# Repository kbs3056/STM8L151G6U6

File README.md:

# STM8L151G6U6
STM8L151GxUx development board.

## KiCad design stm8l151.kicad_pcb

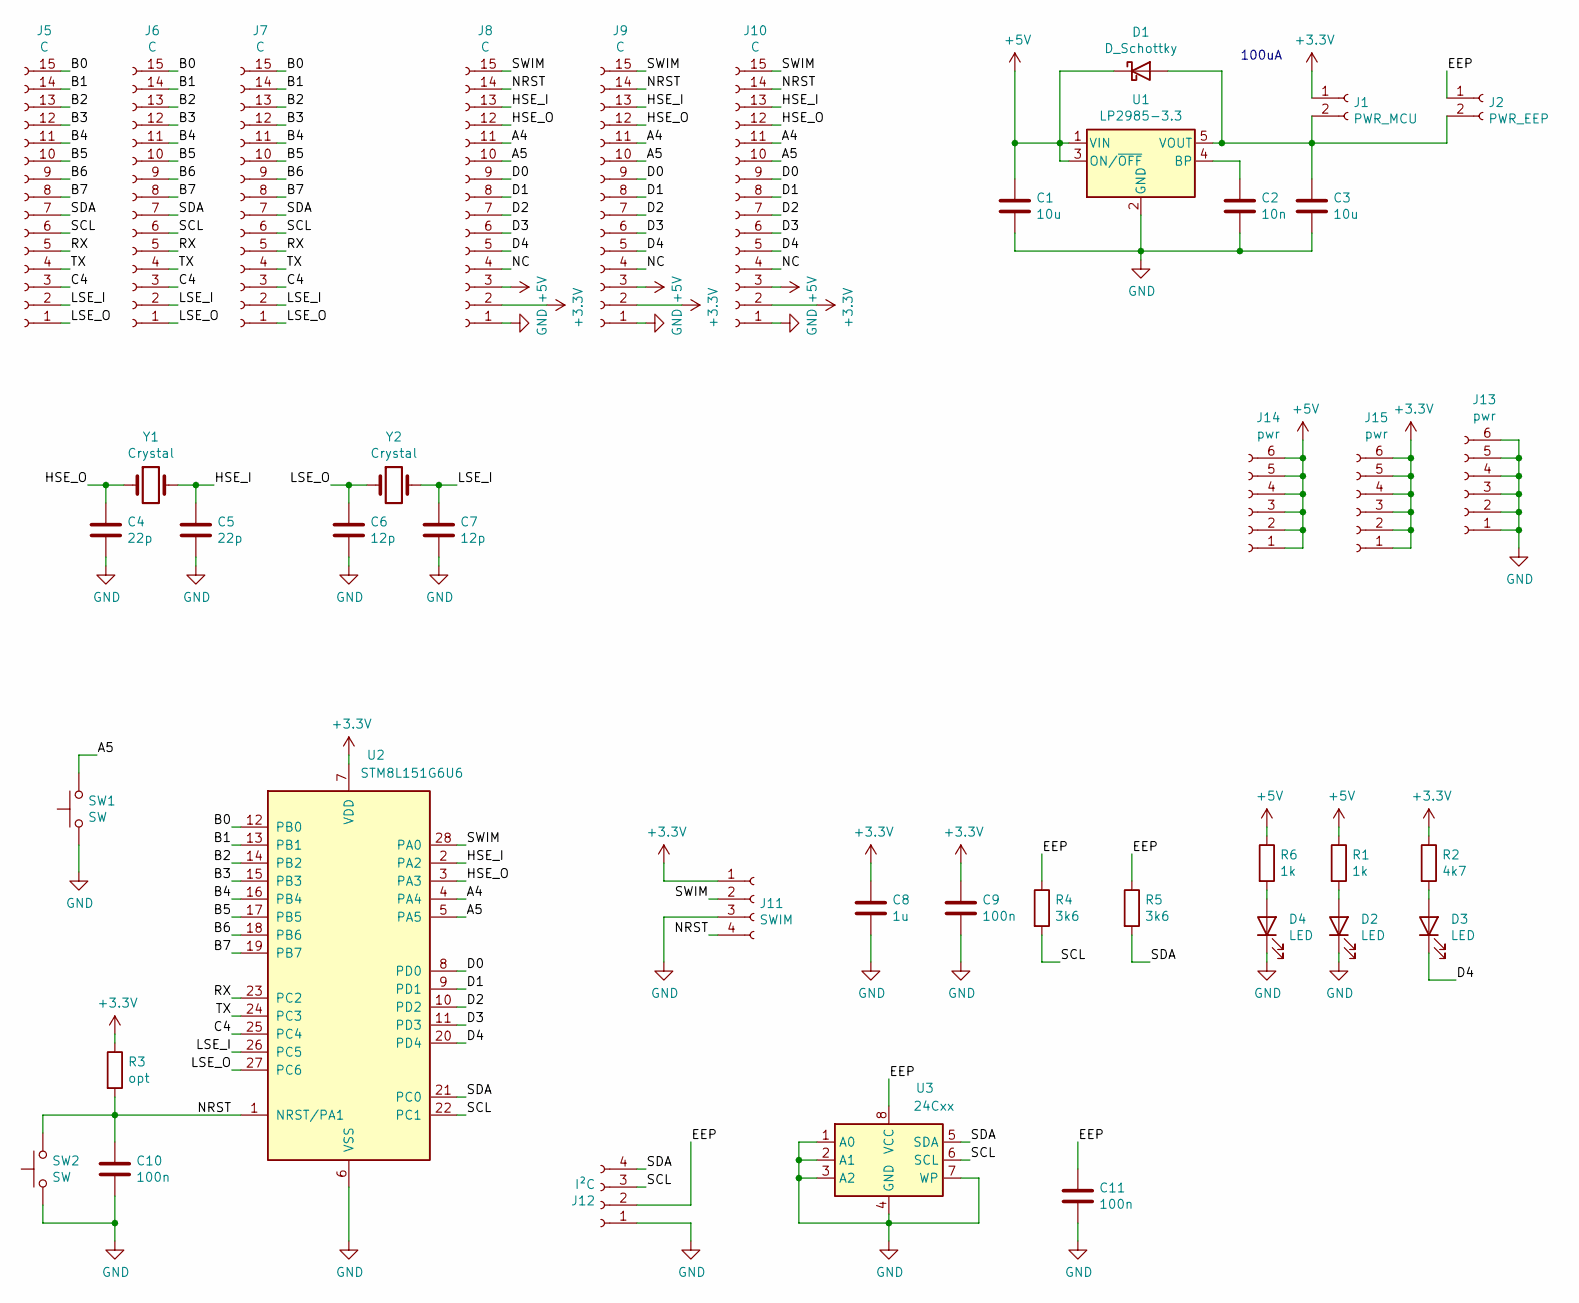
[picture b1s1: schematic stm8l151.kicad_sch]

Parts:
C1, C3: 10u; C_1206_3216Metric
C2: 10n; C_0805_2012Metric
C4, C5: 22p; C_0805_2012Metric
C6, C7: 12p; C_0805_2012Metric
C8: 1u; C_1206_3216Metric
C9, C10, C11: 100n; C_0805_2012Metric
D1: D_Schottky; D_MiniMELF
D2, D3, D4: LED; LED_0805_2012Metric
J1: PWR_MCU; PinSocket_1x02_P2.54mm_Vertical
J2: PWR_EEP; PinSocket_1x02_P2.54mm_Vertical
J5, J6, J7, J8, J9, J10: C; PinSocket_1x15_P2.54mm_Vertical
J11: SWIM; PinSocket_1x04_P2.54mm_Vertical
J12: I²C; PinSocket_1x04_P2.54mm_Vertical
J13, J14, J15: pwr; PinSocket_1x06_P2.54mm_Vertical
R1, R6: 1k; R_1206_3216Metric
R2: 4k7; R_1206_3216Metric
R3: opt; R_1206_3216Metric
R4, R5: 3k6; R_1206_3216Metric
SW1, SW2: SW; SW_SPST_CK_RS282G05A3
U1: LP2985-3.3; SOT-23-5
U2: STM8L151G6U6; QFN-28_4x4mm_P0.5mm
U3: 24Cxx; SOIC-8_5.23x5.23mm_P1.27mm
Y1: Crystal; Crystal_HC49-U_Horizontal
Y2: Crystal; Crystal_C26-LF_D2.1mm_L6.5mm_Horizontal

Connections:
+3V3: C8.1, C9.1, J1.1, J8.2, J9.2, J10.2, J11.1, J15.1, J15.2, J15.3, J15.4, J15.5, J15.6, R2.1, R3.1, U2.7 (VDD)
+5V: C1.1, D1.1 (K), J8.3, J9.3, J10.3, J14.1, J14.2, J14.3, J14.4, J14.5, J14.6, R1.1, R6.1, U1.1 (VIN), U1.3 (ON/~OFF)
/A4: J8.11, J9.11, J10.11, U2.4 (PA4)
/A5: J8.10, J9.10, J10.10, SW1.2, U2.5 (PA5)
/B0: J5.15, J6.15, J7.15, U2.12 (PB0)
/B1: J5.14, J6.14, J7.14, U2.13 (PB1)
/B2: J5.13, J6.13, J7.13, U2.14 (PB2)
/B3: J5.12, J6.12, J7.12, U2.15 (PB3)
/B4: J5.11, J6.11, J7.11, U2.16 (PB4)
/B5: J5.10, J6.10, J7.10, U2.17 (PB5)
/B6: J5.9, J6.9, J7.9, U2.18 (PB6)
/B7: J5.8, J6.8, J7.8, U2.19 (PB7)
/C4: J5.3, J6.3, J7.3, U2.25 (PC4)
/D0: J8.9, J9.9, J10.9, U2.8 (PD0)
/D1: J8.8, J9.8, J10.8, U2.9 (PD1)
/D2: J8.7, J9.7, J10.7, U2.10 (PD2)
/D3: J8.6, J9.6, J10.6, U2.11 (PD3)
/D4: D3.1 (K), J8.5, J9.5, J10.5, U2.20 (PD4)
/EEP: C11.1, J2.1, J12.2, R4.1, R5.1, U3.8 (VCC)
/HSE_I: C5.1, J8.13, J9.13, J10.13, U2.2 (PA2), Y1.2
/HSE_O: C4.1, J8.12, J9.12, J10.12, U2.3 (PA3), Y1.1
/LSE_I: C7.1, J5.2, J6.2, J7.2, U2.26 (PC5), Y2.2
/LSE_O: C6.1, J5.1, J6.1, J7.1, U2.27 (PC6), Y2.1
/NC: J8.4, J9.4, J10.4
/NRST: C10.1, J8.14, J9.14, J10.14, J11.4, R3.2, SW2.2, U2.1 (NRST/PA1)
/RX: J5.5, J6.5, J7.5, U2.23 (PC2)
/SCL: J5.6, J6.6, J7.6, J12.3, R4.2, U2.22 (PC1), U3.6 (SCL)
/SDA: J5.7, J6.7, J7.7, J12.4, R5.2, U2.21 (PC0), U3.5 (SDA)
/SWIM: J8.15, J9.15, J10.15, J11.2, U2.28 (PA0)
/TX: J5.4, J6.4, J7.4, U2.24 (PC3)
GND: C1.2, C2.2, C3.2, C4.2, C5.2, C6.2, C7.2, C8.2, C9.2, C10.2, C11.2, D2.1 (K), D4.1 (K), J8.1, J9.1, J10.1, J11.3, J12.1, J13.1, J13.2, J13.3, J13.4, J13.5, J13.6, SW1.1, SW2.1, U1.2 (GND), U2.6 (VSS), U3.1 (A0), U3.2 (A1), U3.3 (A2), U3.4 (GND), U3.7 (WP)
unnamed: C2.1, U1.4 (BP)
unnamed: C3.1, D1.2 (A), J1.2, J2.2, U1.5 (VOUT)
unnamed: D2.2 (A), R1.2
unnamed: D3.2 (A), R2.2
unnamed: D4.2 (A), R6.2

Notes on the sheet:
100uA

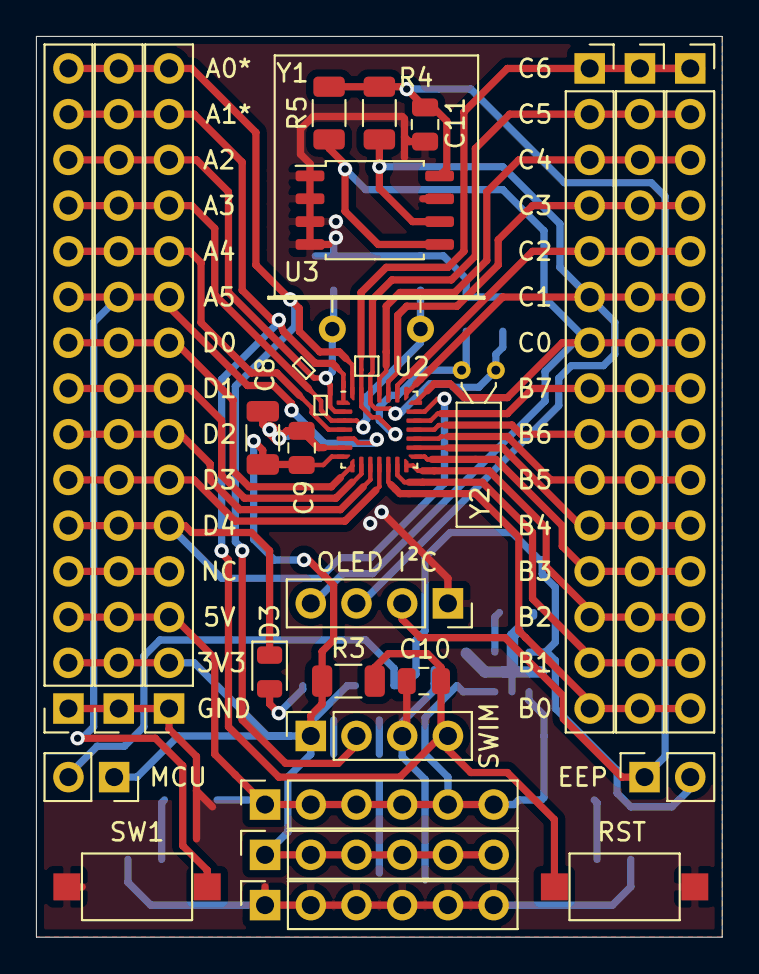
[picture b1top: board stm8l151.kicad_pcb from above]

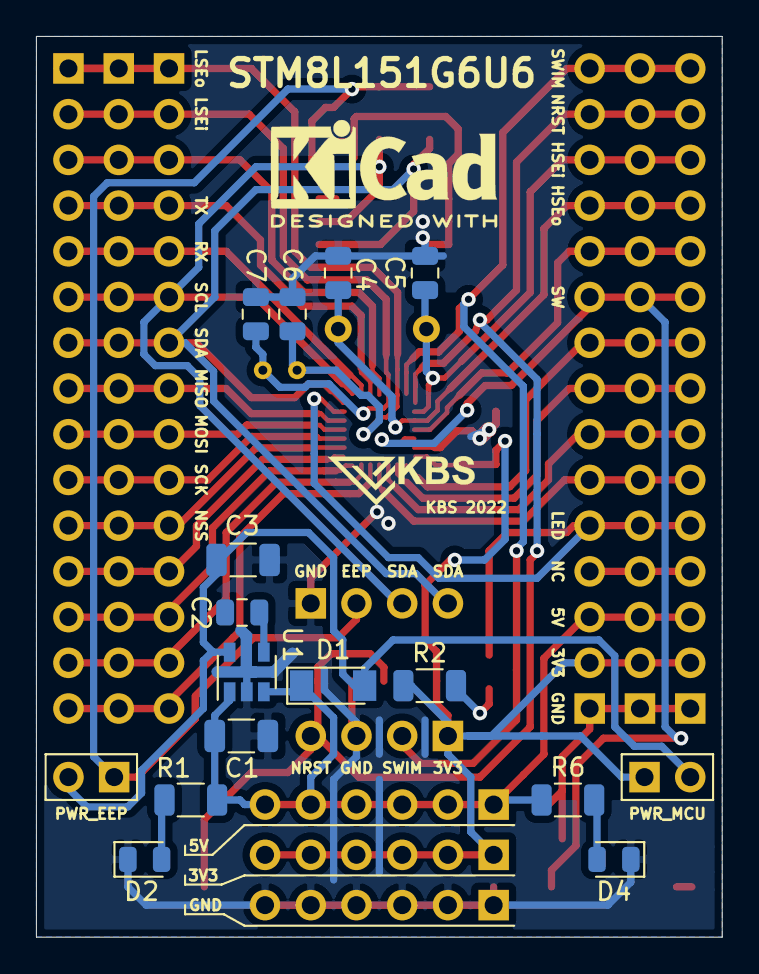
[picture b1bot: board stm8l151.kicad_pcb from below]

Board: 2 copper layers, 38.1 x 50.0 mm, 41 parts (14 on the bottom side), 36 nets.
